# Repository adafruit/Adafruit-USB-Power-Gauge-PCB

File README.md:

## Adafruit USB Power Gauge PCB (Discontinued)

PCB files for the Adafruit USB Power Gauge. Format is EagleCAD schematic and board layout
* https://www.adafruit.com/product/1549

### Description

**This product is currently discontinued.** - This little USB port go-between is like a speed gauge for your USB devices. Instead of hauling out a multimeter and splicing cables, plug this in between for a quick reading on how much current is being drawn from the port. Great for seeing the charge rate of your phone or tablet, checking your battery chargers, or other USB powered projects.

There are a few USB power meters out there, The Practical Meter and the USB Spypow. We wanted something that was made for makers: Reprogrammable micro-controller, analog output, TTL serial output for debugging / datalogging and of course, open source.

Data is passed through transparently from end to end, so you can use it with any USB device at any speed. The power line has a 0.1 ohm current sense resistor and an INA169 high-side current sensor that is tracked by a little ATtiny85 chip. The microcontroller is programmed to read the current draw as well as the bus voltage and light up the strip of LEDs on the side.

The blue LEDs will light up, one for each Watt of power draw (which is ~200mA at 5V nominal), with a couple levels of PWM dimming for increasing current. You can measure up to 1A of current draw - most USB ports are rated for 500mA. It's safe to use this with something that draws up to 2 A of current, it'll just 'max out' the LEDs.

The green LED is helpful to tell if you have too much droop on your power line. It stays lit as long as the voltage is higher than 4.5V, most devices won't charge effectively once it goes below that so if the green LED goes out, you know you should check your port, shorten the USB cable, or reduce the current draw.

As an awesome extra, we also print out the voltage, current and wattage data as readable text on the TX pin at 9600 baud. Connect an FTDI friend, USB console cable, microcontroller, XBee, whatever you want that can read 9600 baud TTL serial data for datalogging, plotting or display.

Comes as a mini kit with an assembled & tested PCB plus a separate USB jack and plug as shown above. Before use, solder the jack and plug. It'll only take you a few minutes and can be done with any soldering iron. Or, advanced users can splice it between a USB extension cable.

Please note: this is a handy gadget but it isn't a multimeter! We do some basic calibration during test, but the serial output readings are not precise and should be used as a basic guide rather than lab-grade data plots. Assume a variance of at least 0.1V and 50mA due to noise, thermal changes, etc.

### License

Adafruit invests time and resources providing this open source design, please support Adafruit and open-source hardware by purchasing products from [Adafruit](https://www.adafruit.com)!

Designed by Limor Fried/Ladyada for Adafruit Industries.

Creative Commons Attribution/Share-Alike, all text above must be included in any redistribution. See license.txt for additional details.

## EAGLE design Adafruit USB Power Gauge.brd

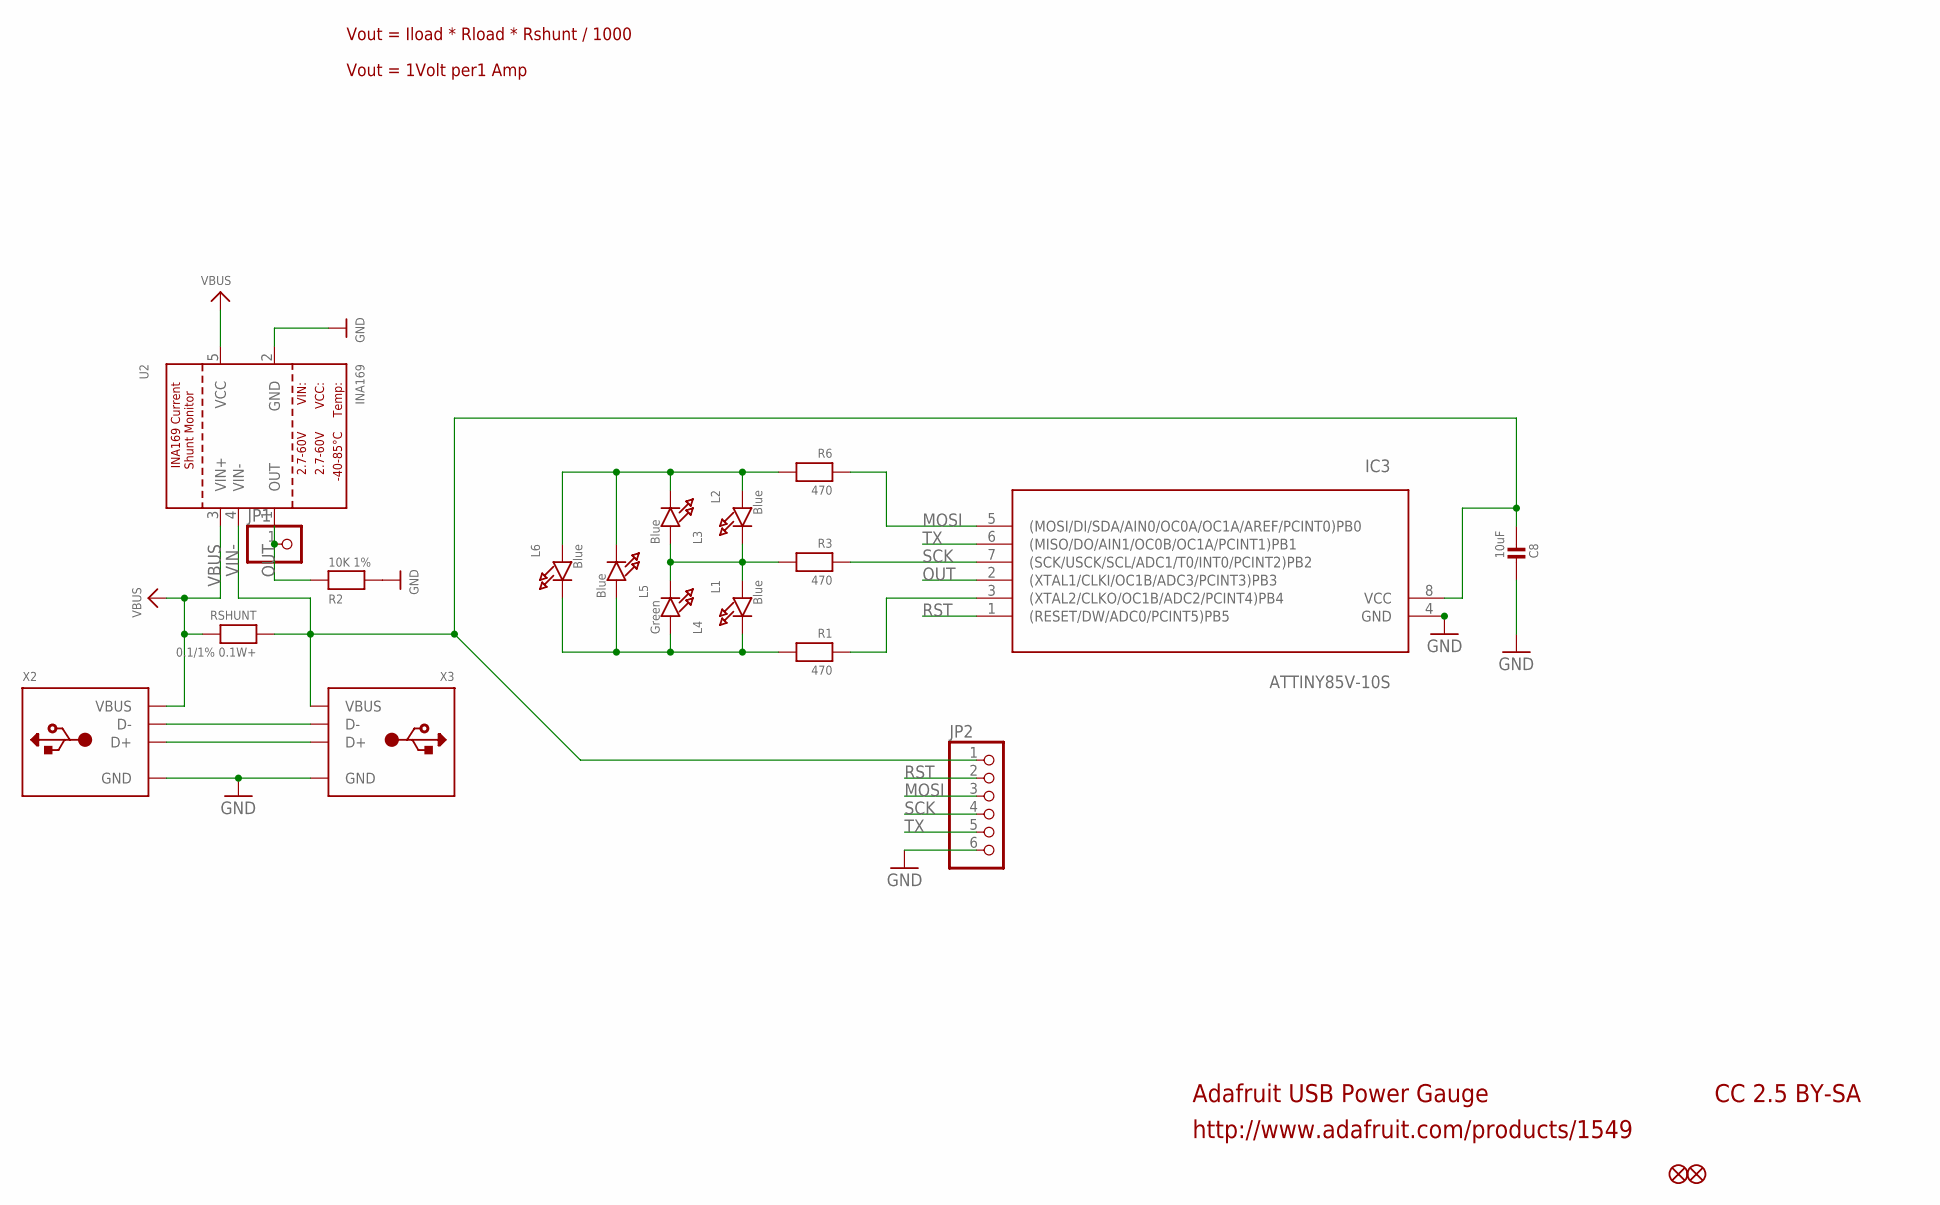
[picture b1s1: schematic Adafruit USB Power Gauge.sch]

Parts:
C8: 10uF; 0805-NO
FID1, FID2: FIDUCIAL""; FIDUCIAL_1MM
IC3: ATTINY85V-10S; SOIC8
JP1: PINHD-1X1CB; 1X01-CLEANBIG
JP2: PINHD-1X6CB; 1X06-CLEANBIG
L1, L2, L3, L5, L6: Blue; CHIPLED_0805_NOOUTLINE
L4: Green; CHIPLED_0805_NOOUTLINE
R1, R3, R6: 470; 0805-NO
R2: 10K 1%; 0805-NO
RSHUNT: 0.1/1% 0.1W+; 0805-NO
U2: INA169; SOT23-5
X2: USB_TYPEA_CLIENTTHM; USB_A-THM
X3: USB_TYPEAPTHFML; USB_HOST-PTH

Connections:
GND: C8.2, IC3.4 (GND), JP2.6, R2.2, U2.2 (GND), X2.GND, X3.GND
MOSI: IC3.5 ((MOSI/DI/SDA/AIN0/OC0A/OC1A/AREF/PCINT0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), JP2.3, R6.1
unnamed: X2.D+, X3.D+
unnamed: L1.C, L4.A, L5.A, L6.C, R1.2
unnamed: X2.D-, X3.D-
unnamed: L1.A, L2.C, L3.A, L4.C, R3.2
unnamed: L2.A, L3.C, L5.C, L6.A, R6.2
unnamed: IC3.3 ((XTAL2/CLKO/OC1B/ADC2/PCINT4)PB4), R1.1
OUT: IC3.2 ((XTAL1/CLKI/OC1B/ADC3/PCINT3)PB3), JP1.1, R2.1, U2.1 (OUT)
RST: IC3.1 ((RESET/DW/ADC0/PCINT5)PB5), JP2.2
SCK: IC3.7 ((SCK/USCK/SCL/ADC1/T0/INT0/PCINT2)PB2), JP2.4, R3.1
TX: IC3.6 ((MISO/DO/AIN1/OC0B/OC1A/PCINT1)PB1), JP2.5
VBUS: RSHUNT.2, U2.3 (VIN+), U2.5 (VCC), X2.VBUS
VIN-: C8.1, IC3.8 (VCC), JP2.1, RSHUNT.1, U2.4 (VIN-), X3.VBUS

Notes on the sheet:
Adafruit USB Power Gauge
http://www.adafruit.com/products/1549
CC 2.5 BY-SA
Vout = Iload * Rload * Rshunt / 1000
Vout = 1Volt per1 Amp

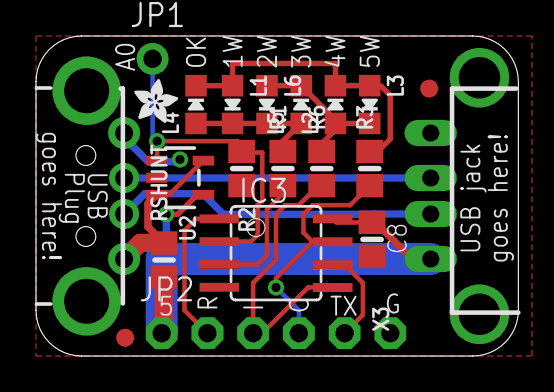
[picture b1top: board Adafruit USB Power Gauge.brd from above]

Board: 2 copper layers, 26.8 x 17.8 mm, 21 parts (0 on the bottom side), 14 nets.

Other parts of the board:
U$3: ADAFRUIT_2.5MM

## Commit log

2017-10-29 init

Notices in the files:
parts and their libraries:
microbuilder: This work is placed in the public domain, and may be freely used for commercial and non-commercial work with the following conditions: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
